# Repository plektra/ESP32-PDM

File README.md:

# ESP32-PDM

An open, low-cost power distribution module for boats: solid-state outputs controlled both by ordinary
panel switches and over NMEA 2000, with current and fault reporting. Built around an ESP32-S3 and
Infineon PROFET+24V high-side switches, for 12 V and 24 V systems, assembled by JLCPCB.

**Status:** Both boards (`hardware/pdm-4ch`, `hardware/pdm-hc2`) are complete at schematic level and pass ERC
(apart from library-version notices). The `pdm-4ch` PCB is fully routed (0 DRC errors, 0 unconnected); the image
above is rendered from it. Not tested in hardware. A first firmware for `pdm-4ch` (`firmware/`) builds and passes its host tests; it has not run on a board. `pdm-4ch` goes first as a prototype, with `pdm-hc2` layout
after its bring-up.

## Boards

| Board | Channels | Output stage | Continuous current per channel (estimate, 40 °C, vented) |
|---|---|---|---|
| `pdm-4ch` | 4 | Infineon PROFET+24V BTT6050-1ERA (first version, 16 A in total) | ≈ 4 A |
| `pdm-hc2` | 2 | TI TPS48110A-Q1 + back-to-back MOSFETs, built-in breaker ≈ 17.5 A / 146 ms (≈ 15–20 A over tolerances) | ≈ 15 A |

Both boards share the controller, power, NMEA 2000 and switch-input design.

## Population and ordering rule (`pdm-4ch`)

The first version of `pdm-4ch` is built with four BTT6050-1ERA (≈ 4 A per channel, 16 A in total). Heavy loads go on
`pdm-hc2`. A BTT6010-1ERA (≈ 8 A) option may return in a later revision; it is not supported on this version.

## Features

- Physical switch inputs drive the outputs directly in hardware: they keep working if the ESP32 or
  its 3.3 V supply fails. Surge-protected, 12 V and 24 V, suitable for long switch cables.
- NMEA 2000 (isolated CAN), USB-C for programming, Wi-Fi for Signal K / configuration / OTA.
- Per-channel current measurement and fault reporting.
- Low-power modes controlled over the bus.

## Important limitations

- **Not protected against load dump.** Onboard TVS diodes clamp short transients only. A load dump
  (battery disconnected while an alternator is charging, or a BMS disconnect) must be handled at system
  level: alternator protection device, field-disconnect battery switch, or a BMS that signals the
  charge source before disconnecting. Like most marine electronics, this device relies on that.
- **Not a circuit breaker.** Every output wire must be protected by a fuse or breaker sized to the
  wire. The switches protect themselves, not your wiring.
- Install in an enclosed, ventilated location; observe the continuous current ratings.
- **Panel switches: dry contacts only.** Use plain (unlit) switch contacts. A lamp or LED across the contacts leaks
  current that can switch the output on in hardware. Use the J5 LED lines for panel indication instead.
- **12 V systems, engine cranking:** the panel-switch path switches an output off when the switch voltage drops below
  about 8 V (about 8.5 V at the battery). While the engine cranks, panel-switched outputs such as navigation lights can
  therefore go off for a moment. 24 V systems are not affected.
- **Reverse battery (`pdm-4ch`):** a reverse-blocking MOSFET in the supply input (Q30 with controller U30) keeps
  a reversed battery of up to 30 V away from the rest of the board, with no time limit: the bulk capacitor, the
  output switches, the panel switches and the loads see no reverse voltage. Above about 33 V the input surge diode
  conducts and the battery fuse must clear. If that MOSFET has failed short, the old limits apply: only the output
  switches survive (at most 28 V, under 2 minutes, each load at least 12 Ω), and the bulk capacitor C31 is not rated
  for reverse voltage and can overheat and vent. So check the polarity before connecting.
- **`pdm-hc2` external breaker (required):** each HC2 output must have its own external breaker or fuse that trips at
  **at most 15–18 A** (within minutes), in addition to the wire protection above. The built-in breaker trips at about
  17.5 A (≈ 15–20 A over part tolerances) only after 146 ms; between the 15 A rating and that level the board relies on
  the external breaker and the firmware soft fuse. The board label states the same. A bilge-pump output's breaker sits
  between J11 and the junction with the float-switch circuit, so the float circuit never depends on the PDM. That
  breaker must open before the float-circuit fuse: make it clearly smaller, or use a slower float fuse. Otherwise a
  short on the PDM side can also take out the float circuit.
- **`pdm-hc2` reverse battery destroys the board:** a reversed battery connection destroys both HC2 output controllers
  (TPS48110A-Q1, rated −1 V). There is no reverse-polarity protection on this revision. Use the keyed/polarised
  battery connector J10 only as marked, check polarity before connecting; the board label carries this warning.
- **Mounting:** two ways, on the same four M3 holes. On a DIN rail the bare board goes on a plastic carrier, edge-on, about 36 mm
  of rail per unit, inside an enclosure you provide; it must keep out drips and loose metal, and carrier and screws must never
  touch board copper. All connectors are keyed plugs that pull out from the board edge: wire them on the bench and leave room for the plug and cable bend. Exception: on the `pdm-4ch` prototype the battery connector J10 is a fixed screw terminal. Switch off the battery feed before unscrewing it, and on a DIN rail wire it before the neighbouring unit is fitted. Connect it only as marked: a reversed battery up to 30 V is blocked on the board, but check polarity before connecting.
  Alternatively use a vented 3D-printed enclosure, also for flat mounting. Each board gives off about 9 W at full load: in a
  shared enclosure keep the air inside at or below 50 °C for the full rating (estimate until measured), or derate.
- **Cable entry and strain relief:** no connector plug may carry a cable's weight or pull. Support every cable near the
  unit (a cable tie on the DIN mount's anchors, or the enclosure's glands and clamp), with a drip loop below the entry.
  The printed enclosure takes power and output cables through nylon glands and the thin panel wires through a clamp
  comb, all from the bottom face; the NMEA 2000 drop cable plugs into an M12 5-pin panel connector, whose shield pin is
  not connected: do not tie the drop's shield to anything at the PDM.
- **Board input limits:** at most **16 A** continuous through J10 on `pdm-4ch` and **36 A** on `pdm-hc2`, whatever the
  outputs could draw together. Size the battery feed, and its fuse, so that these limits are not exceeded.
- **`pdm-hc2` timing:** after power is connected, the first switch-on of each output (also from a panel switch)
  takes about 0.1 s. After an overcurrent or short-circuit trip the output stays off for about 4 minutes and then
  tries again. HC2 outputs are on/off only (no dimming/PWM).
- **`pdm-hc2` loads:** HC2 is for motor loads (bilge pumps, wipers) and LED work lights, one light per output. Each HC2 output is
  rated for at most **about 50 µF of load input capacitance** (to be confirmed on the prototype). A larger capacitive
  load can trip the short-circuit protection at switch-on, and the output then stays off for about 4 minutes. Put
  DC-DC converters (e.g. 24→12 V for a car radio), radios and other electronics on `pdm-4ch`. Put several lights on one
  output only if they have little capacitance (plain LED strips without their own driver) or a test shows the group
  switches on cleanly from warm; if a group trips at switch-on, split it over several outputs.
- **USB-C is a service port only.** Connect only a battery-powered laptop, or use a USB isolator. The
  board's GND is the boat's battery negative. A laptop on a shore-powered charger can tie its protective
  earth to battery negative through the USB cable, which can cause ground-loop currents, galvanic
  corrosion and damage. Unplug the USB cable after service.

## Installation

The interference immunity of the boards assumes the cable practice below. It adds to the points in
[Important limitations](#important-limitations) (load dump, wire fuses, dry contacts, reverse battery, the `pdm-hc2`
external breaker, USB service only), which are not repeated here.

- **Battery feed.** Fuse at the battery, sized to the wire. Run + and − as a twisted or tightly bundled pair, as short
  as possible, at least 0.5 m from the VHF antenna feed and the transmitter; where they must cross, cross at 90°.
  Check polarity before connecting (see the reverse-battery points above).
- **Loads.** Run each load's return with its feed (same cable, twisted) back to the battery negative bus. Never return
  load current through the PDM ground. Fuse each output wire (see "Not a circuit breaker" above).
- **Inductive loads** (solenoids, relays, horns, motors): fit a diode or TVS at the load.
- **PWM.** No PWM above 200 Hz on `pdm-4ch`. No PWM at all on `pdm-hc2` until it has been measured on the bench
  (its outputs are on/off only, see above).
- **Panel cable.** One screened multicore, at most 10 m, with the switch, LED and supply wires inside the same cable.
  Connect the drain only at the PDM end (J5.10). Dry contacts only (see above). Do not share the cable with other
  loads.
- **NMEA 2000.** Drop cable at most 6 m; ground the backbone shield once, at the power tap. The node has no shield pin,
  so do not connect the drain at the node. Keep the drop away from the VHF coax.
- **Position.** An enclosed, vented box (see above), as far from the VHF antenna and its coax as practical. The plastic
  box gives no shielding: the cables act as the antenna, so cable practice matters more than box position.

## Repository layout

```
hardware/pdm-4ch/   KiCad project, 4-channel board (PROFET)
hardware/pdm-hc2/   KiCad project, 2-channel high-current board
lib/                shared KiCad symbols and footprints
docs/               CONTINUE-FROM-HERE (next steps), decisions, ARCHITECTURE, design notes, reviews
tools/              heat budget model, schematic editing helpers, netlist checker
.claude/            Claude Code roles: commands and review agents (see docs/WORKING-WITH-CLAUDE.md)
```

See [docs/design-notes.md](docs/design-notes.md) for the design rationale, heat budget and open items.

## History

This repository supersedes the earlier two-board design (base board + output module):
[ESP32-PDM-base](https://github.com/plektra/ESP32-PDM-base) and
[ESP32-PDM-4x4](https://github.com/plektra/ESP32-PDM-4x4).

## License

Hardware (schematics, PCB, fabrication files, documentation, library parts): [CERN-OHL-S v2](LICENSE).
Software (`tools/`, board scripts, firmware): [MIT](LICENSE-MIT). Third-party 3D models and KiCad stock-library
parts keep their own terms. Versions up to commit `1799052` (2026-11-17) were released under MIT. Details, and the
source-location notice for anyone who makes boards from these files: [NOTICE.md](NOTICE.md).

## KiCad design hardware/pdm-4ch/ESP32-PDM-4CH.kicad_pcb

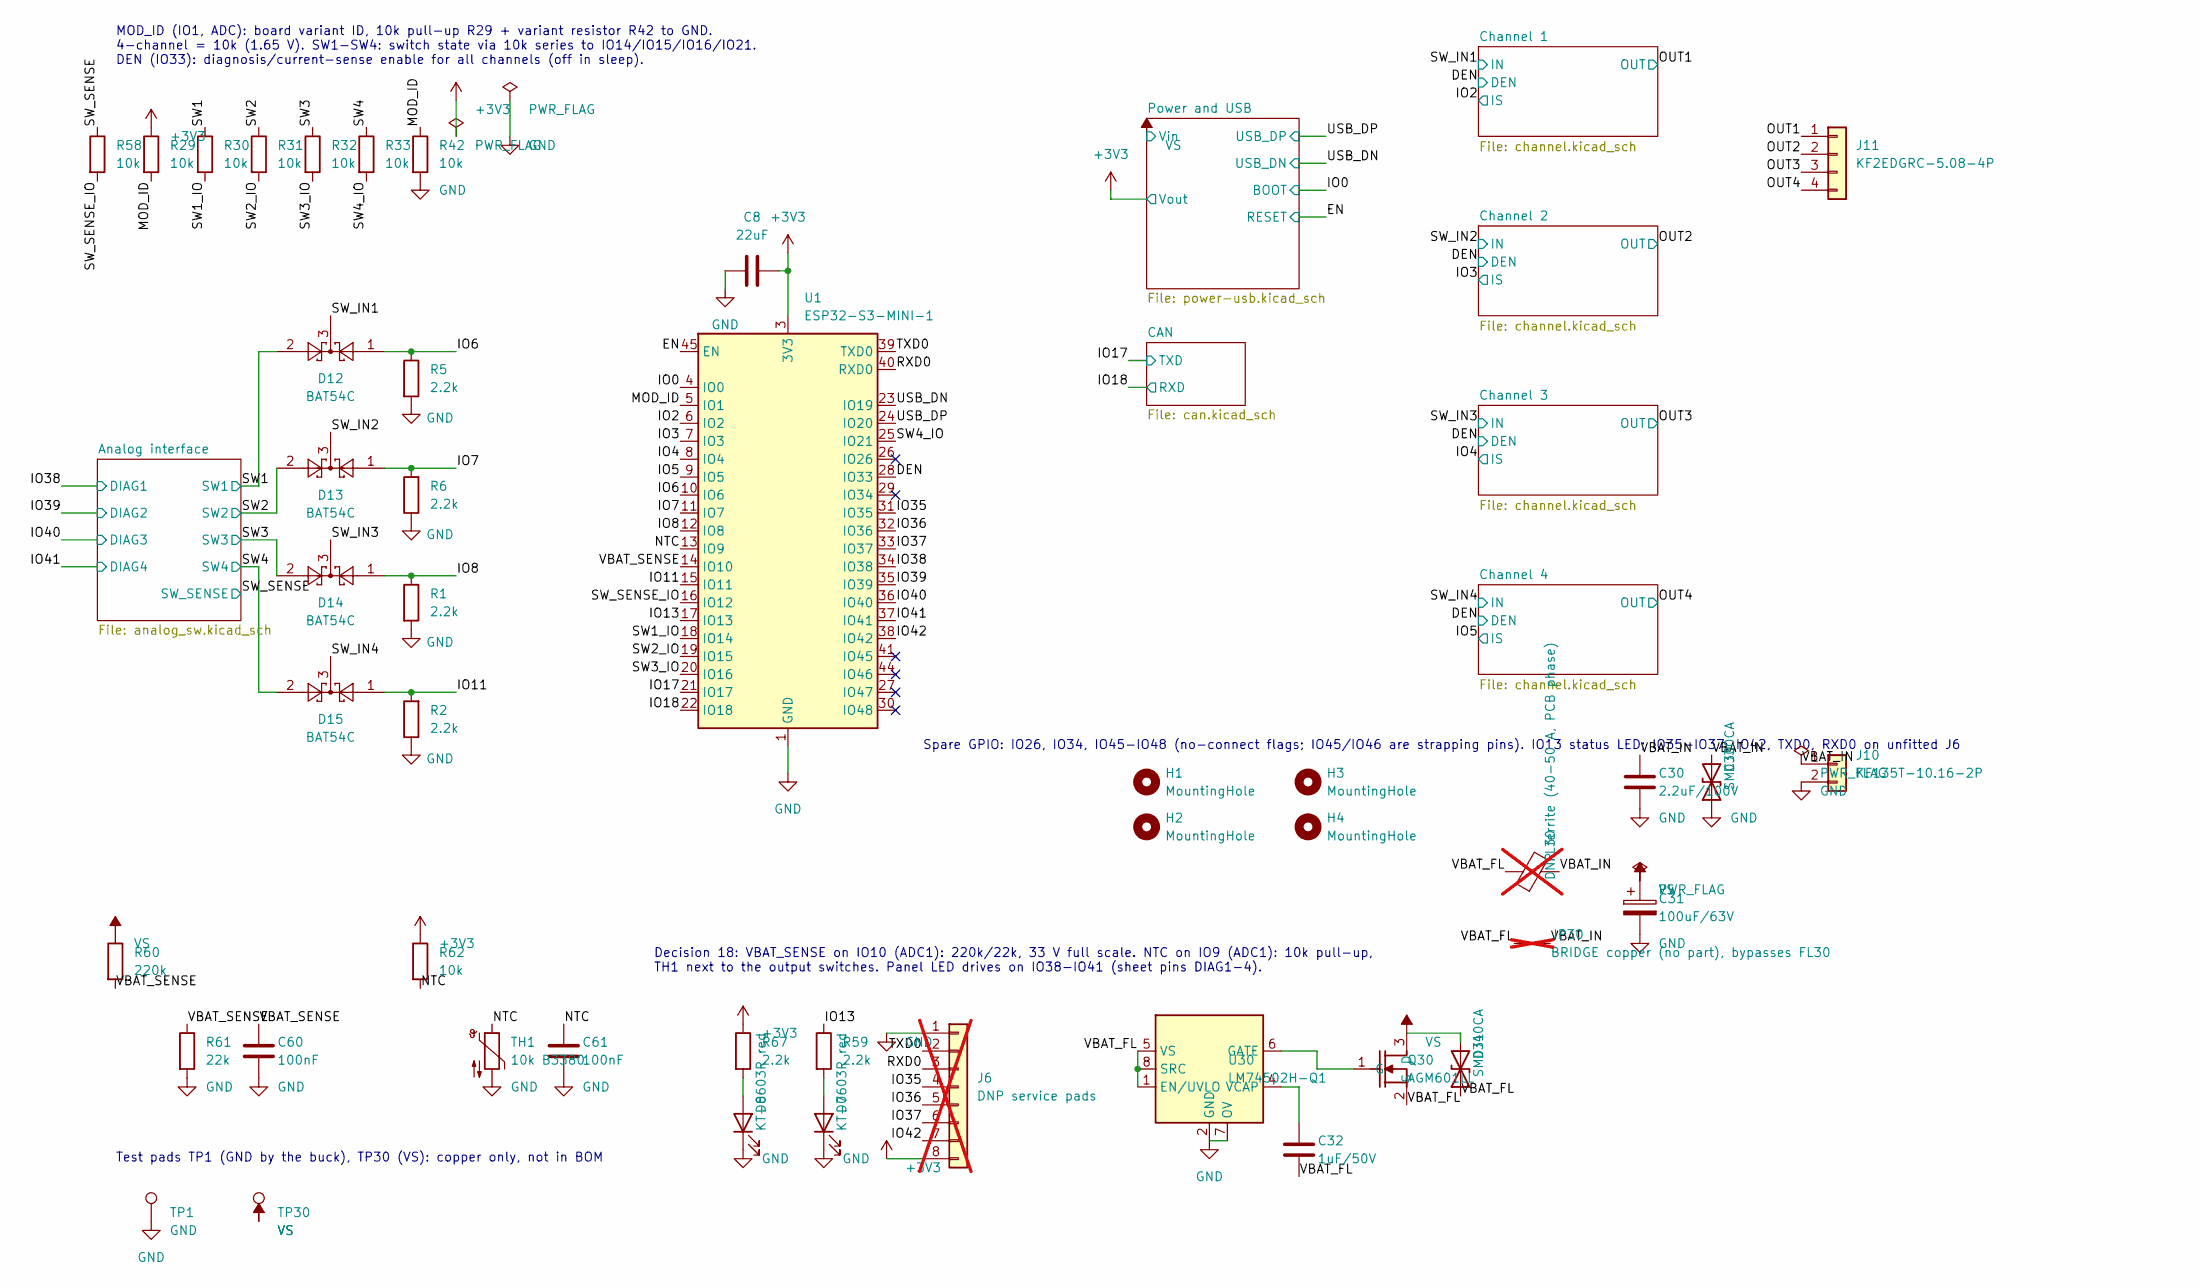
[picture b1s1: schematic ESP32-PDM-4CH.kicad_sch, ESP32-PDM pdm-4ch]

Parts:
C8: 22uF; C_0805_2012Metric; LCSC C45783
C30: 2.2uF/100V; C_1206_3216Metric; MPN Samsung CL31B225KCHSNNE; LCSC C170101
C31: 100uF/63V; CP_Elec_8x10; MPN Ymin VKMD1001J101MV; LCSC C487384
C32: 1uF/50V; C_0603_1608Metric; LCSC C15849
C60, C61: 100nF; C_0402_1005Metric; LCSC C307331
D7, D8: KT-0603R red; LED_0603_1608Metric; LCSC C2286
D12, D13, D14, D15: BAT54C; SOT-23; LCSC C22466350
D30: SMCJ30CA; D_SMC; LCSC C19077607
D31: SMDJ40CA; D_SMC; LCSC C42371557
FL30: DNP ferrite (40-50 A, PCB phase); not fitted
H1, H2, H3, H4: MountingHole; MountingHole_3.2mm_M3
J6: DNP service pads; PinHeader_1x08_P2.54mm_Vertical; not fitted
J10: KF135T-10.16-2P; Kefa_KF135T-10.16-2P; LCSC C475108
J11: KF2EDGRC-5.08-4P; Kefa_KF2EDGRC-5.08-4P; LCSC C441238
JP30: BRIDGE copper (no part), bypasses FL30; NetTie-2_SMD_Pad2.0mm; not fitted
Q30: AGM601LL; Infineon_PG-HSOF-8-1; LCSC C5464765
R1, R2, R5, R6, R59, R67: 2.2k; R_0402_1005Metric; LCSC C25879
R29, R30, R31, R32, R33, R42, R58, R62: 10k; R_0402_1005Metric; LCSC C25744
R60: 220k; R_0402_1005Metric; LCSC C25767
R61: 22k; R_0402_1005Metric; LCSC C25768
TH1: 10k B3380; R_0603_1608Metric; LCSC C52155402
TP1: GND; TestPoint_Pad_D1.0mm
TP30: VS; TestPoint_Pad_D1.0mm
U1: ESP32-S3-MINI-1; ESP32-S2-MINI-1; LCSC C2913206
U30: LM74502H-Q1; TI_DDF0008A; MPN LM74502HQDDFRQ1; LCSC C5219203

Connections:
+3V3: C8.2, J6.8, R29.1, R62.1, R67.1, U1.3 (3V3); also elsewhere on the board
/DEN: U1.28 (IO33); also elsewhere on the board
/EN: U1.45 (EN); also elsewhere on the board
/IO0: U1.4 (IO0); also elsewhere on the board
/IO2: U1.6 (IO2); also elsewhere on the board
/IO3: U1.7 (IO3); also elsewhere on the board
/IO4: U1.8 (IO4); also elsewhere on the board
/IO5: U1.9 (IO5); also elsewhere on the board
/IO6: D12.1, R5.1, U1.10 (IO6)
/IO7: D13.1, R6.2, U1.11 (IO7)
/IO8: D14.1, R1.1, U1.12 (IO8)
/IO11: D15.1, R2.2, U1.15 (IO11)
/IO13: R59.1, U1.17 (IO13)
/IO17: U1.21 (IO17); also elsewhere on the board
/IO18: U1.22 (IO18); also elsewhere on the board
/IO35: J6.4, U1.31 (IO35)
/IO36: J6.5, U1.32 (IO36)
/IO37: J6.6, U1.33 (IO37)
/IO38: U1.34 (IO38); also elsewhere on the board
/IO39: U1.35 (IO39); also elsewhere on the board
/IO40: U1.36 (IO40); also elsewhere on the board
/IO41: U1.37 (IO41); also elsewhere on the board
/IO42: J6.7, U1.38 (IO42)
/MOD_ID: R29.2, R42.1, U1.5 (IO1)
/NTC: C61.1, R62.2, TH1.1, U1.13 (IO9)
/OUT1: J11.1; also elsewhere on the board
/OUT2: J11.2; also elsewhere on the board
/OUT3: J11.3; also elsewhere on the board
/OUT4: J11.4; also elsewhere on the board
/RXD0: J6.3, U1.40 (RXD0)
/SW1: D12.2, R30.1; also elsewhere on the board
/SW1_IO: R30.2, U1.18 (IO14)
/SW2: D13.2, R31.1; also elsewhere on the board
/SW2_IO: R31.2, U1.19 (IO15)
/SW3: D14.2, R32.1; also elsewhere on the board
/SW3_IO: R32.2, U1.20 (IO16)
/SW4: D15.2, R33.1; also elsewhere on the board
/SW4_IO: R33.2, U1.25 (IO21)
/SW_IN1: D12.3; also elsewhere on the board
/SW_IN2: D13.3; also elsewhere on the board
/SW_IN3: D14.3; also elsewhere on the board
/SW_IN4: D15.3; also elsewhere on the board
/SW_SENSE: R58.1; also elsewhere on the board
/SW_SENSE_IO: R58.2, U1.16 (IO12)
/TXD0: J6.2, U1.39 (TXD0)
/USB_DN: U1.23 (IO19); also elsewhere on the board
/USB_DP: U1.24 (IO20); also elsewhere on the board
/VBAT_FL: C32.2, D31.1 (A1), FL30.1, JP30.1, Q30.2 (S), U30.1 (EN/UVLO), U30.5 (VS), U30.8 (SRC)
/VBAT_IN: C30.1, D30.2 (A2), FL30.2, J10.1, JP30.2
/VBAT_SENSE: C60.1, R60.2, R61.1, U1.14 (IO10)
GND: C8.1, C30.2, C31.2, C60.2, C61.2, D7.1 (K), D8.1 (K), D30.1 (A1), J6.1, J10.2, R1.2, R2.1, R5.2, R6.1, R42.2, R61.2, TH1.2, TP1.1, U1.1 (GND), U1.2 (GND), U1.42 (GND), U1.43 (GND), U1.46 (GND), U1.47 (GND), U1.48 (GND), U1.49 (GND), U1.50 (GND), U1.51 (GND), U1.52 (GND), U1.53 (GND), U1.54 (GND), U1.55 (GND), U1.56 (GND), U1.57 (GND), U1.58 (GND), U1.59 (GND), U1.60 (GND), U1.61 (GND), U1.62 (GND), U1.63 (GND), U1.64 (GND), U1.65 (GND), U30.2 (GND), U30.7 (OV); also elsewhere on the board
unnamed: D7.2 (A), R59.2
unnamed: D8.2 (A), R67.2
unnamed: Q30.1 (G), U30.6 (GATE)
unnamed: C32.1, U30.4 (VCAP)
VS: C31.1, D31.2 (A2), Q30.3 (D), R60.1, TP30.1; also elsewhere on the board

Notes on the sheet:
MOD_ID (IO1, ADC): board variant ID, 10k pull-up R29 + variant resistor R42 to GND. 4-channel = 10k (1.65 V). SW1-SW4: switch state via 10k series to IO14/IO15/IO16/IO21. DEN (IO33): diagnosis/current-sense enable for all channels (off in sleep).
Spare GPIO: IO26, IO34, IO45-IO48 (no-connect flags; IO45/IO46 are strapping pins). IO13 status LED; IO35-IO37, IO42, TXD0, RXD0 on unfitted J6
Decision 18: VBAT_SENSE on IO10 (ADC1): 220k/22k, 33 V full scale. NTC on IO9 (ADC1): 10k pull-up, TH1 next to the output switches. Panel LED drives on IO38-IO41 (sheet pins DIAG1-4).
Test pads TP1 (GND by the buck), TP30 (VS): copper only, not in BOM

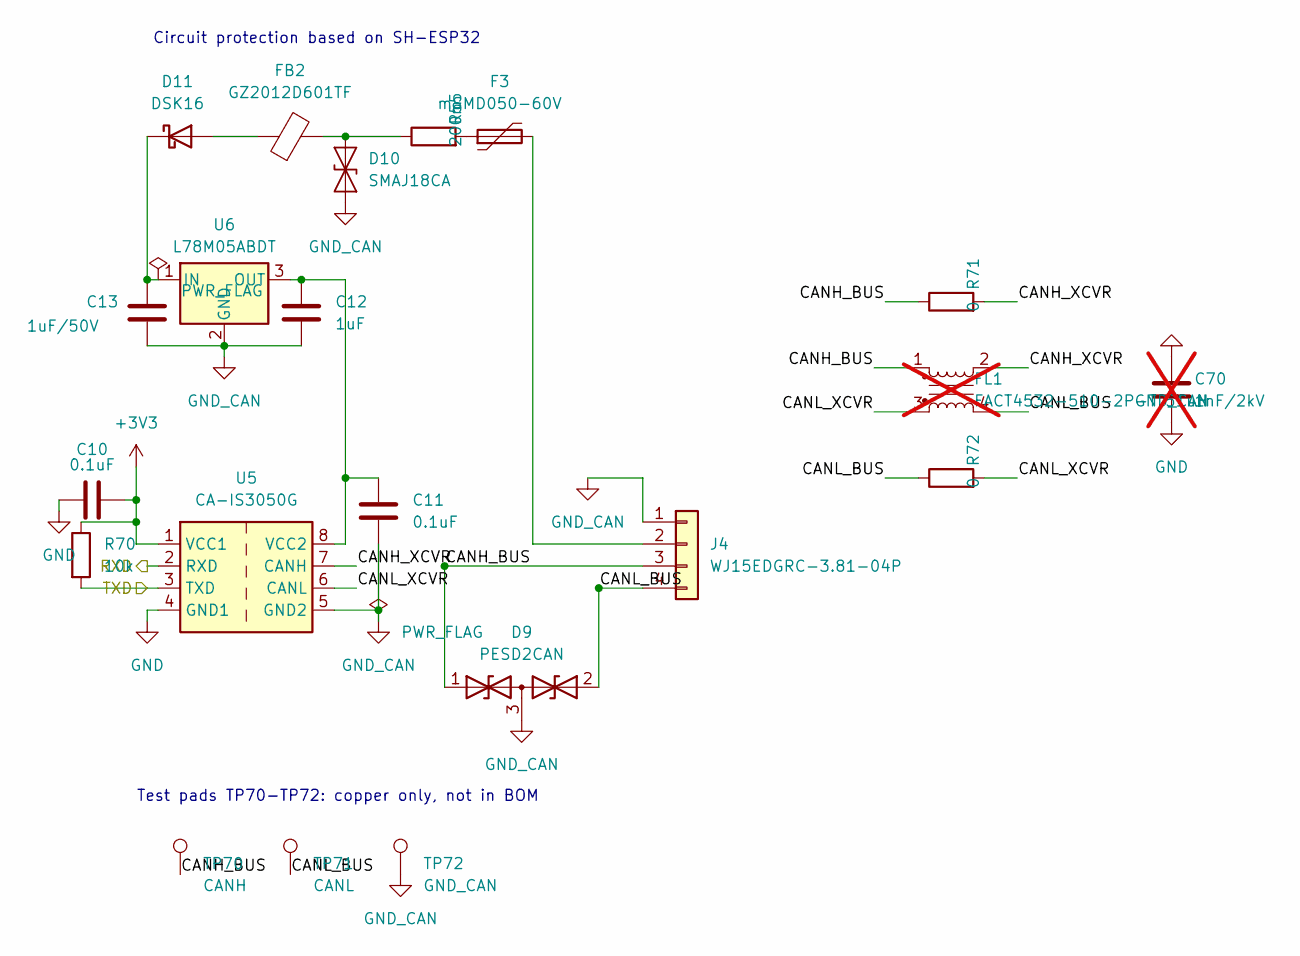
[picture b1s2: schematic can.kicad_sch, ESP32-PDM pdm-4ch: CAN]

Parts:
C10, C11: 0.1uF; C_0402_1005Metric; LCSC C307331
C12: 1uF; C_0603_1608Metric; LCSC C15849
C13: 1uF/50V; C_0805_2012Metric; LCSC C28323
C70: 1nF/2kV; C_1206_3216Metric; LCSC C9196; not fitted
D9: PESD2CAN; SOT-23; LCSC C2687131
D10: SMAJ18CA; D_SMA; LCSC C19077539
D11: DSK16; D_SOD-123F; LCSC C22466351
F3: mSMD050-60V; Fuse_1812_4532Metric; LCSC C70113
FB2: GZ2012D601TF; L_0805_2012Metric; LCSC C1017
FL1: FACT4532-510-2P-T 51uH; L_CommonModeChoke_Coilank_ACM4532; LCSC C20624726; not fitted
J4: WJ15EDGRC-3.81-04P; Kangnex_WJ15EDGRC-3.81-04P; LCSC C7245
R55: 200m; R_2512_6332Metric; LCSC C7420022
R70: 10k; R_0402_1005Metric; LCSC C25744
R71, R72: 0; R_0402_1005Metric; LCSC C17168
TP70: CANH; TestPoint_Pad_D1.0mm
TP71: CANL; TestPoint_Pad_D1.0mm
TP72: GND_CAN; TestPoint_Pad_D1.0mm
U5: CA-IS3050G; SOIC-8_7.5x5.85mm_P1.27mm; LCSC C528763
U6: L78M05ABDT; TO-252-2; LCSC C58069

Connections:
+3V3: C10.2, R70.1, U5.1 (VCC1); also elsewhere on the board
/CAN/CANH_BUS: D9.1 (A1), FL1.1, J4.3, R71.1, TP70.1
/CAN/CANH_XCVR: FL1.2, R71.2, U5.7 (CANH)
/CAN/CANL_BUS: D9.2 (A2), FL1.4, J4.4, R72.1, TP71.1
/CAN/CANL_XCVR: FL1.3, R72.2, U5.6 (CANL)
/IO17: R70.2, U5.3 (TXD); also elsewhere on the board
/IO18: U5.2 (RXD); also elsewhere on the board
GND: C10.1, C70.2, U5.4 (GND1); also elsewhere on the board
GND_CAN: C11.2, C12.2, C13.2, C70.1, D9.3 (common), D10.1 (A1), J4.1, TP72.1, U5.5 (GND2), U6.2 (GND)
unnamed: D10.2 (A2), FB2.2, R55.1
unnamed: D11.2 (A), FB2.1
unnamed: C13.1, D11.1 (K), U6.1 (IN)
unnamed: F3.1, R55.2
unnamed: F3.2, J4.2
unnamed: C11.1, C12.1, U5.8 (VCC2), U6.3 (OUT)

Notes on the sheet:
Circuit protection based on SH-ESP32
Test pads TP70-TP72: copper only, not in BOM

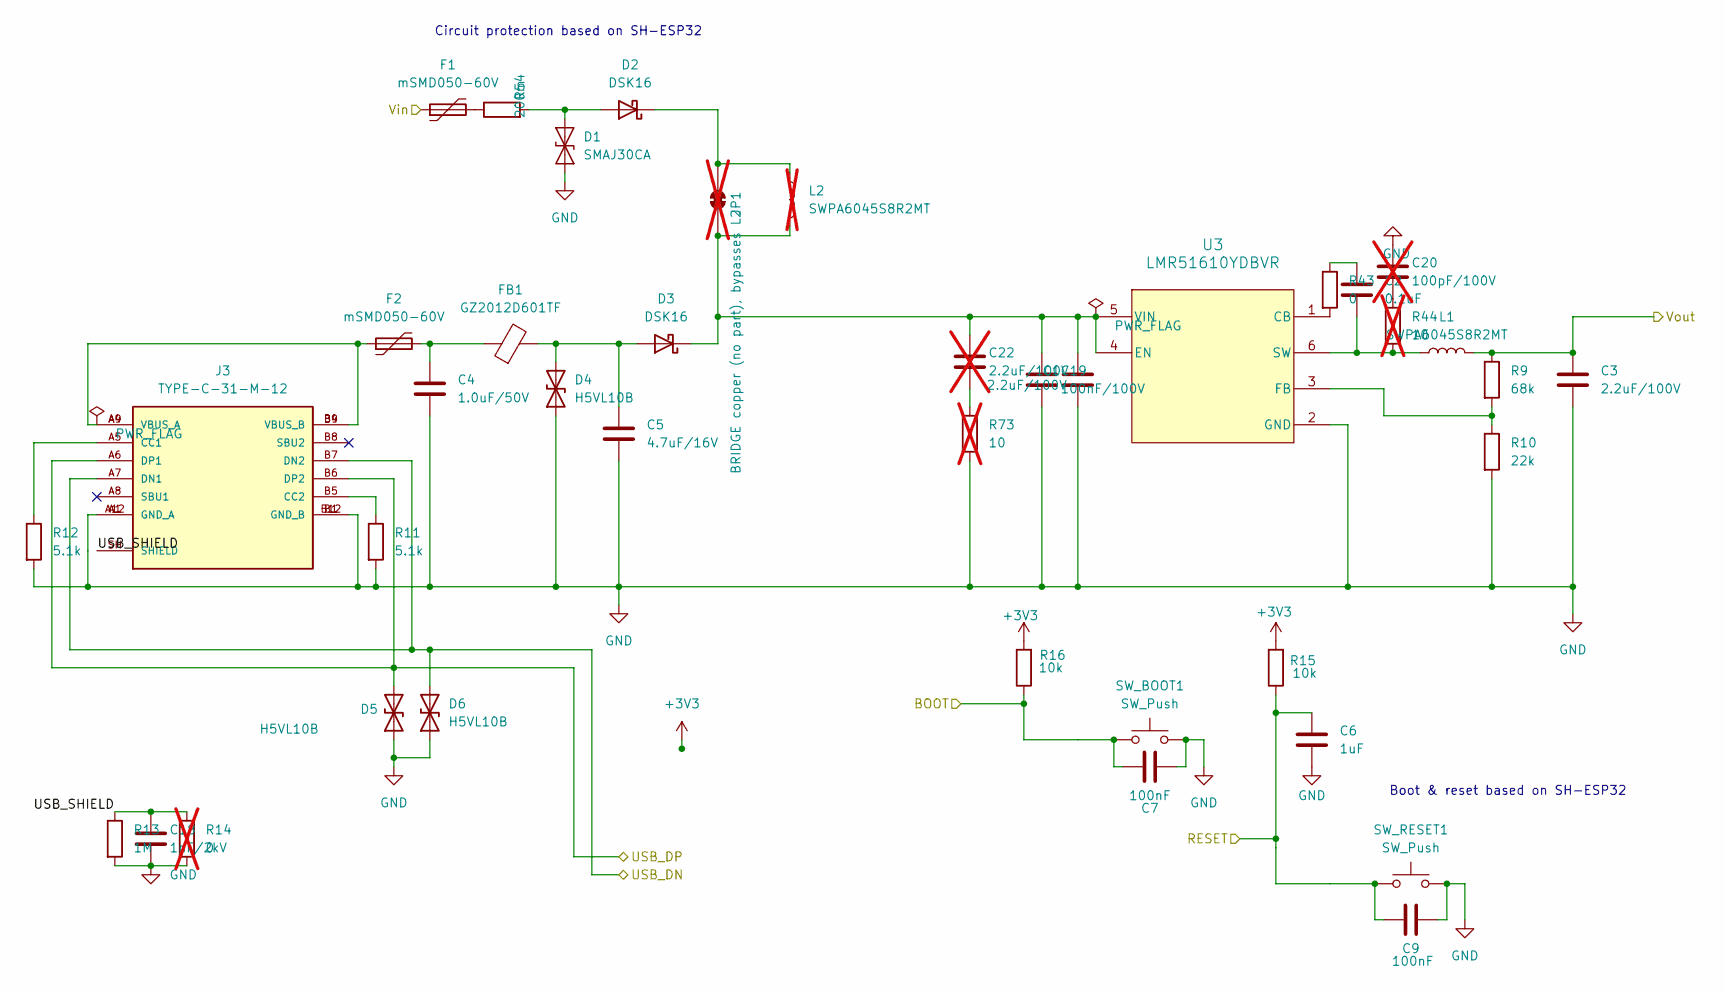
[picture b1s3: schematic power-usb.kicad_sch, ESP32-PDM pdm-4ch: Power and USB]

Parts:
C1, C3: 2.2uF/100V; C_1206_3216Metric; LCSC C170101
C2: 0.1uF; C_0402_1005Metric; LCSC C307331
C4: 1.0uF/50V; C_0603_1608Metric; LCSC C15849
C5: 4.7uF/16V; C_0603_1608Metric; LCSC C19666
C6: 1uF; C_0603_1608Metric; LCSC C15849
C7, C9: 100nF; C_0805_2012Metric; LCSC C28233
C18: 1nF/2kV; C_1206_3216Metric; LCSC C9196
C19: 100nF/100V; C_0805_2012Metric; LCSC C28233
C20: 100pF/100V; C_0603_1608Metric; LCSC C296717; not fitted
C22: 2.2uF/100V; C_1206_3216Metric; LCSC C170101; not fitted
D1: SMAJ30CA; D_SMA; LCSC C19077548
D2, D3: DSK16; D_SOD-123F; LCSC C22466351
D4, D5, D6: H5VL10B; D_SOD-882; LCSC C7420372
F1, F2: mSMD050-60V; Fuse_1812_4532Metric; LCSC C70113
FB1: GZ2012D601TF; L_0805_2012Metric; LCSC C1017
J3: TYPE-C-31-M-12; USB_C_Receptacle_HRO_TYPE-C-31-M-12; PARTREV A2; LCSC C165948
JP1: BRIDGE copper (no part), bypasses L2; SolderJumper-2_P1.3mm_Bridged_Pad1.0x1.5mm; not fitted
L1: SWPA6045S8R2MT; L_Sunlord_SWPA6045S; LCSC C96963
L2: SWPA6045S8R2MT; L_Sunlord_SWPA6045S; LCSC C96963; not fitted
R9: 68k; R_0402_1005Metric; LCSC C36871
R10: 22k; R_0402_1005Metric; LCSC C25768
R11, R12: 5.1k; R_0402_1005Metric; LCSC C25905
R13: 1M; R_1206_3216Metric; LCSC C17927
R14: 0; R_0603_1608Metric; LCSC C21189; not fitted
R15, R16: 10k; R_0402_1005Metric; LCSC C25744
R43: 0; R_0402_1005Metric; LCSC C17168
R44, R73: 10; R_1206_3216Metric; LCSC C17903; not fitted
R54: 200m; R_2512_6332Metric; LCSC C7420022
SW_BOOT1: SW_Push; SW_Push_1P1T_XKB_TS-1187A; LCSC C318884
SW_RESET1: SW_Push; SW_Push_1P1T_XKB_TS-1187A; LCSC C318884
U3: LMR51610YDBVR; SOT-23-6; LCSC C22427220

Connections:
+3V3: C3.1, L1.2, R9.1, R15.2, R16.2; also elsewhere on the board
/EN: C6.1, C9.1, R15.1, SW_RESET1.1; also elsewhere on the board
/IO0: C7.2, R16.1, SW_BOOT1.1; also elsewhere on the board
/Power and USB/USB_SHIELD: C18.1, J3.SH (SHIELD), R13.1, R14.1
/USB_DN: D6.2 (A2), J3.A7 (DN1), J3.B7 (DN2); also elsewhere on the board
/USB_DP: D5.2 (A2), J3.A6 (DP1), J3.B6 (DP2); also elsewhere on the board
GND: C1.1, C3.2, C4.2, C5.2, C6.2, C7.1, C9.2, C18.2, C19.2, C20.1, D1.1 (A1), D4.1 (A1), D5.1 (A1), D6.1 (A1), J3.A1 (GND_A), J3.A12 (GND_A), J3.B1 (GND_B), J3.B12 (GND_B), R10.2, R11.2, R12.2, R13.2, R14.2, R73.2, SW_BOOT1.2, SW_RESET1.2, U3.2 (GND); also elsewhere on the board
unnamed: C2.1, R43.1
unnamed: C4.1, F2.2, FB1.1
unnamed: C20.2, R44.1
unnamed: C22.2, R73.1
unnamed: D1.2 (A2), D2.2 (A), R54.2
unnamed: D2.1 (K), JP1.1 (A), L2.1
unnamed: C5.1, D3.2 (A), D4.2 (A2), FB1.2
unnamed: C1.2, C19.1, C22.1, D3.1 (K), JP1.2 (B), L2.2, U3.4 (EN), U3.5 (VIN)
unnamed: F1.2, R54.1
unnamed: F2.1, J3.A4 (VBUS_A), J3.A9 (VBUS_A), J3.B4 (VBUS_B), J3.B9 (VBUS_B)
unnamed: J3.A5 (CC1), R12.1
unnamed: J3.B5 (CC2), R11.1
unnamed: R43.2, U3.1 (CB)
unnamed: R9.2, R10.1, U3.3 (FB)
unnamed: C2.2, L1.1, R44.2, U3.6 (SW)
VS: F1.1; also elsewhere on the board

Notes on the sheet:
Circuit protection based on SH-ESP32
Boot & reset based on SH-ESP32

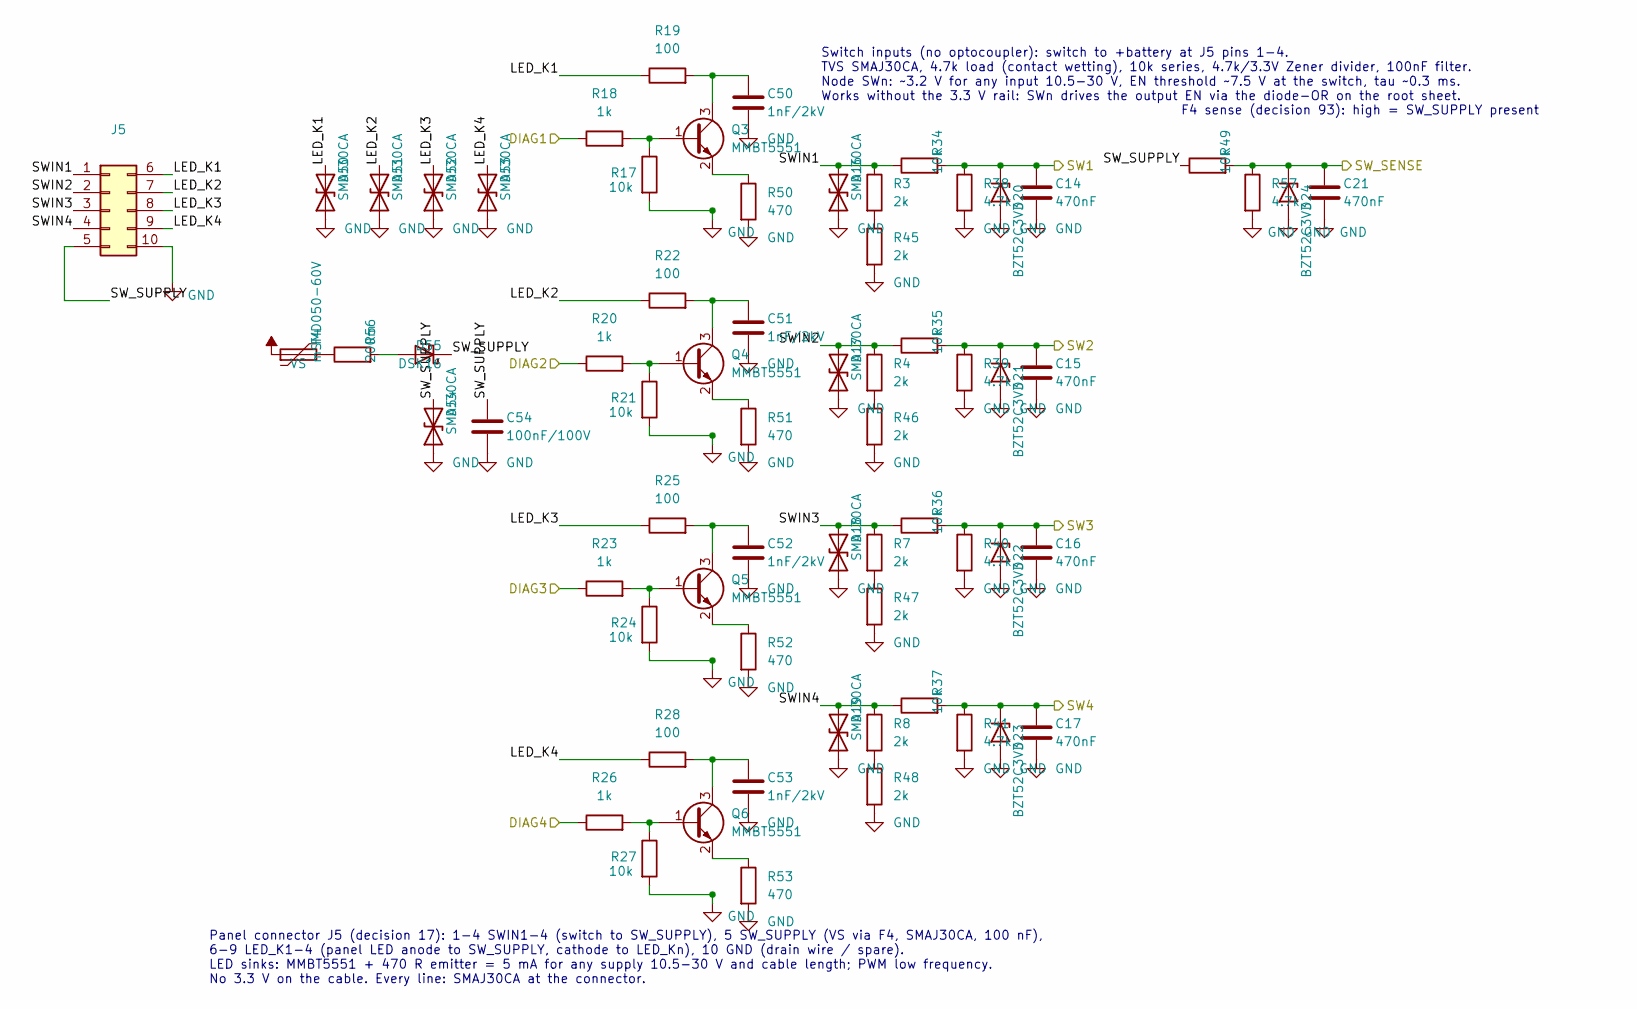
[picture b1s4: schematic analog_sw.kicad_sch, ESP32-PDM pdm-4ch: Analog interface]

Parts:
C14, C15, C16, C17, C21: 470nF; C_0402_1005Metric; LCSC C47339
C50, C51, C52, C53: 1nF/2kV; C_1206_3216Metric; LCSC C9196
C54: 100nF/100V; C_0805_2012Metric; LCSC C28233
D16, D17, D18, D19, D50, D51, D52, D53, D54: SMAJ30CA; D_SMA; LCSC C19077548
D20, D21, D22, D23, D24: BZT52C3V3; D_SOD-123; LCSC C19077396
D55: DSK16; D_SOD-123F; LCSC C22466351
F4: mSMD050-60V; Fuse_1812_4532Metric; LCSC C70113
J5: WJ15EDGRC-3.81-10P; Kangnex_WJ15EDGRC-3.81-10P; LCSC C26895
Q3, Q4, Q5, Q6: MMBT5551; SOT-23-3; LCSC C2145
R3, R4, R7, R8, R45, R46, R47, R48: 2k; R_1206_3216Metric; LCSC C17944
R17, R21, R24, R27: 10k; R_0402_1005Metric; LCSC C25744
R18, R20, R23, R26: 1k; R_0402_1005Metric; LCSC C11702
R19, R22, R25, R28: 100; R_0402_1005Metric; LCSC C25076
R34, R35, R36, R37, R49: 10k; R_1206_3216Metric; LCSC C17902
R38, R39, R40, R41, R57: 4.7k; R_0402_1005Metric; LCSC C25900
R50, R51, R52, R53: 470; R_0402_1005Metric; LCSC C25117
R56: 200m; R_2512_6332Metric; LCSC C7420022

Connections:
/Analog interface/LED_K1: D50.2 (A2), J5.6, R19.1
/Analog interface/LED_K2: D51.2 (A2), J5.7, R22.1
/Analog interface/LED_K3: D52.2 (A2), J5.8, R25.1
/Analog interface/LED_K4: D53.2 (A2), J5.9, R28.1
/Analog interface/SWIN1: D16.2 (A2), J5.1, R3.1, R34.1
/Analog interface/SWIN2: D17.2 (A2), J5.2, R4.1, R35.1
/Analog interface/SWIN3: D18.2 (A2), J5.3, R7.1, R36.1
/Analog interface/SWIN4: D19.2 (A2), J5.4, R8.1, R37.1
/Analog interface/SW_SUPPLY: C54.1, D54.2 (A2), D55.1 (K), J5.5, R49.1
/IO38: R18.1; also elsewhere on the board
/IO39: R20.1; also elsewhere on the board
/IO40: R23.1; also elsewhere on the board
/IO41: R26.1; also elsewhere on the board
/SW1: C14.1, D20.1 (K), R34.2, R38.1; also elsewhere on the board
/SW2: C15.1, D21.1 (K), R35.2, R39.1; also elsewhere on the board
/SW3: C16.1, D22.1 (K), R36.2, R40.1; also elsewhere on the board
/SW4: C17.1, D23.1 (K), R37.2, R41.1; also elsewhere on the board
/SW_SENSE: C21.1, D24.1 (K), R49.2, R57.1; also elsewhere on the board
GND: C14.2, C15.2, C16.2, C17.2, C21.2, C50.2, C51.2, C52.2, C53.2, C54.2, D16.1 (A1), D17.1 (A1), D18.1 (A1), D19.1 (A1), D20.2 (A), D21.2 (A), D22.2 (A), D23.2 (A), D24.2 (A), D50.1 (A1), D51.1 (A1), D52.1 (A1), D53.1 (A1), D54.1 (A1), J5.10, R17.2, R21.2, R24.2, R27.2, R38.2, R39.2, R40.2, R41.2, R45.2, R46.2, R47.2, R48.2, R50.2, R51.2, R52.2, R53.2, R57.2; also elsewhere on the board
unnamed: D55.2 (A), R56.2
unnamed: F4.2, R56.1
unnamed: Q3.1 (B), R17.1, R18.2
unnamed: C50.1, Q3.3 (C), R19.2
unnamed: Q3.2 (E), R50.1
unnamed: Q4.1 (B), R20.2, R21.1
unnamed: C51.1, Q4.3 (C), R22.2
unnamed: Q4.2 (E), R51.1
unnamed: Q5.1 (B), R23.2, R24.1
unnamed: C52.1, Q5.3 (C), R25.2
unnamed: Q5.2 (E), R52.1
unnamed: Q6.1 (B), R26.2, R27.1
unnamed: C53.1, Q6.3 (C), R28.2
unnamed: Q6.2 (E), R53.1
unnamed: R3.2, R45.1
unnamed: R4.2, R46.1
unnamed: R7.2, R47.1
unnamed: R8.2, R48.1
VS: F4.1; also elsewhere on the board

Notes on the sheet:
Switch inputs (no optocoupler): switch to +battery at J5 pins 1-4. TVS SMAJ30CA, 4.7k load (contact wetting), 10k series, 4.7k/3.3V Zener divider, 100nF filter. Node SWn: ~3.2 V for any input 10.5-30 V, EN threshold ~7.5 V at the switch, tau ~0.3 ms. Works without the 3.3 V rail: SWn drives the out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
Panel connector J5 (decision 17): 1-4 SWIN1-4 (switch to SW_SUPPLY), 5 SW_SUPPLY (VS via F4, SMAJ30CA, 100 nF), 6-9 LED_K1-4 (panel LED anode to SW_SUPPLY, cathode to LED_Kn), 10 GND (drain wire / spare). LED sinks: MMBT5551 + 470 R emitter = 5 mA for any supply 10.5-30 V and cable length; PWM low 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
F4 sense (decision 93): high = SW_SUPPLY present

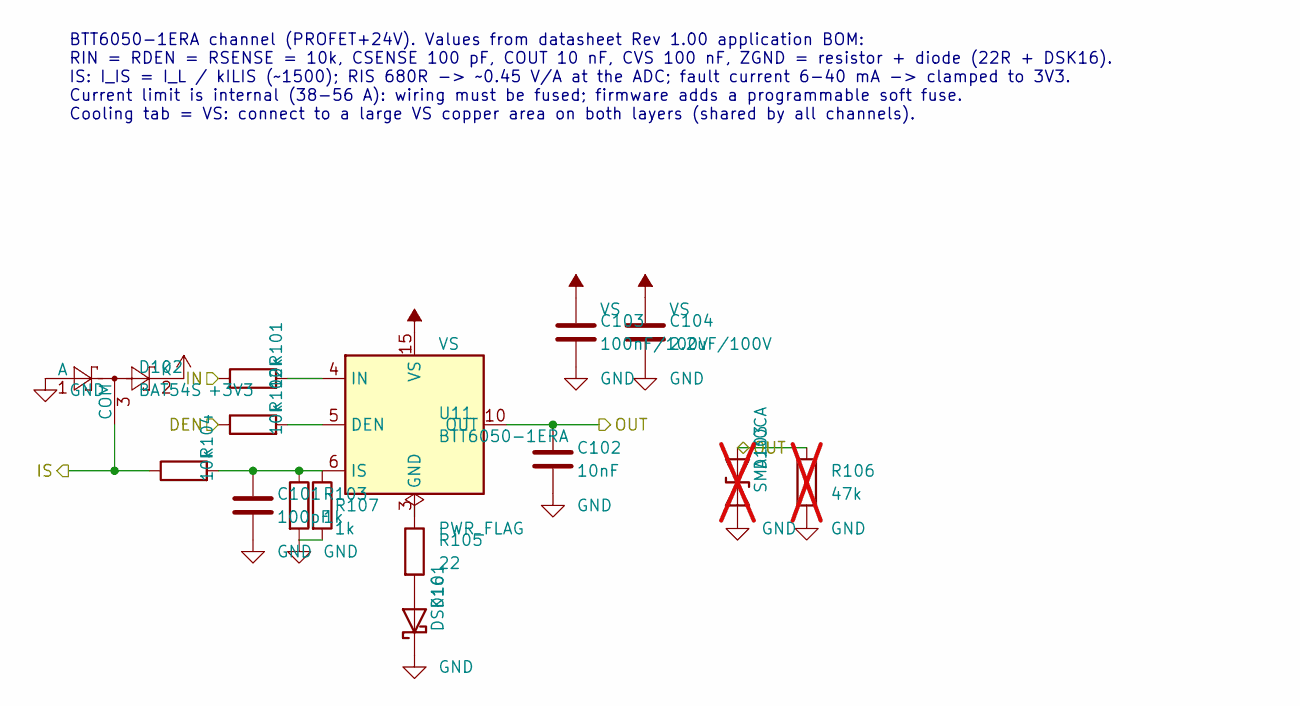
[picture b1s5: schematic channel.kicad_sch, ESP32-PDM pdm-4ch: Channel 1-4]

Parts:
C101: 100pF; C_0402_1005Metric; LCSC C1546
C102: 10nF; C_0402_1005Metric; LCSC C15195
C103: 100nF/100V; C_0805_2012Metric; LCSC C28233
C104: 2.2uF/100V; C_1206_3216Metric; MPN Samsung CL31B225KCHSNNE; LCSC C170101
D101: DSK16; D_SOD-123F; LCSC C22466351
D102: BAT54S; SOT-23; LCSC C7420333
D103: SMAJ30CA; D_SMA; LCSC C19077548; not fitted
R101, R102, R104: 10k; R_0402_1005Metric; LCSC C25744
R103, R107: 1k; R_1206_3216Metric; MPN CRCW12061K00FKEAHP; LCSC C844867
R105: 22; R_0402_1005Metric; LCSC C25092
R106: 47k; R_0603_1608Metric; LCSC C25819; not fitted
U11: BTT6050-1ERA; Infineon_PG-TDSO-14_ThermalVias; LCSC C534868

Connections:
+3V3: D102.2 (K); also elsewhere on the board
/DEN: R102.1; also elsewhere on the board
/IO2: D102.3 (COM), R104.1; also elsewhere on the board
/OUT1: C102.1, D103.2 (A2), R106.1, U11.10 (OUT), U11.11 (OUT), U11.12 (OUT); also elsewhere on the board
/SW_IN1: R101.1; also elsewhere on the board
GND: C101.2, C102.2, C103.2, C104.2, D101.1 (K), D102.1 (A), D103.1 (A1), R103.2, R106.2, R107.2; also elsewhere on the board
unnamed: D101.2 (A), R105.2
unnamed: R102.2, U11.5 (DEN)
unnamed: R105.1, U11.3 (GND)
unnamed: R101.2, U11.4 (IN)
unnamed: C101.1, R103.1, R104.2, R107.1, U11.6 (IS)
VS: C103.1, C104.1, U11.15 (VS); also elsewhere on the board

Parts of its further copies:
C201, C301, C401: 100pF; C_0402_1005Metric; LCSC C1546
C202, C302, C402: 10nF; C_0402_1005Metric; LCSC C15195
C203, C303, C403: 100nF/100V; C_0805_2012Metric; LCSC C28233
C204, C304, C404: 2.2uF/100V; C_1206_3216Metric; MPN Samsung CL31B225KCHSNNE; LCSC C170101
D201, D301, D401: DSK16; D_SOD-123F; LCSC C22466351
D202, D302, D402: BAT54S; SOT-23; LCSC C7420333
D203, D303, D403: SMAJ30CA; D_SMA; LCSC C19077548; not fitted
R201, R202, R204, R301, R302, R304, R401, R402, R404: 10k; R_0402_1005Metric; LCSC C25744
R203, R207, R303, R307, R403, R407: 1k; R_1206_3216Metric; MPN CRCW12061K00FKEAHP; LCSC C844867
R205, R305, R405: 22; R_0402_1005Metric; LCSC C25092
R206, R306, R406: 47k; R_0603_1608Metric; LCSC C25819; not fitted
U12, U13, U14: BTT6050-1ERA; Infineon_PG-TDSO-14_ThermalVias; LCSC C534868

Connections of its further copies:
+3V3: D202.2 (K), D302.2 (K), D402.2 (K); also elsewhere on the board
/DEN: R202.1, R302.1, R402.1; also elsewhere on the board
/IO3: D202.3 (COM), R204.1; also elsewhere on the board
/IO4: D302.3 (COM), R304.1; also elsewhere on the board
/IO5: D402.3 (COM), R404.1; also elsewhere on the board
/OUT2: C202.1, D203.2 (A2), R206.1, U12.10 (OUT), U12.11 (OUT), U12.12 (OUT); also elsewhere on the board
/OUT3: C302.1, D303.2 (A2), R306.1, U13.10 (OUT), U13.11 (OUT), U13.12 (OUT); also elsewhere on the board
/OUT4: C402.1, D403.2 (A2), R406.1, U14.10 (OUT), U14.11 (OUT), U14.12 (OUT); also elsewhere on the board
/SW_IN2: R201.1; also elsewhere on the board
/SW_IN3: R301.1; also elsewhere on the board
/SW_IN4: R401.1; also elsewhere on the board
GND: C201.2, C202.2, C203.2, C204.2, C301.2, C302.2, C303.2, C304.2, C401.2, C402.2, C403.2, C404.2, D201.1 (K), D202.1 (A), D203.1 (A1), D301.1 (K), D302.1 (A), D303.1 (A1), D401.1 (K), D402.1 (A), D403.1 (A1), R203.2, R206.2, R207.2, R303.2, R306.2, R307.2, R403.2, R406.2, R407.2; also elsewhere on the board
unnamed: D201.2 (A), R205.2
unnamed: D301.2 (A), R305.2
unnamed: D401.2 (A), R405.2
unnamed: R202.2, U12.5 (DEN)
unnamed: R205.1, U12.3 (GND)
unnamed: R201.2, U12.4 (IN)
unnamed: C201.1, R203.1, R204.2, R207.1, U12.6 (IS)
unnamed: R302.2, U13.5 (DEN)
unnamed: R305.1, U13.3 (GND)
unnamed: R301.2, U13.4 (IN)
unnamed: C301.1, R303.1, R304.2, R307.1, U13.6 (IS)
unnamed: R402.2, U14.5 (DEN)
unnamed: R405.1, U14.3 (GND)
unnamed: R401.2, U14.4 (IN)
unnamed: C401.1, R403.1, R404.2, R407.1, U14.6 (IS)
VS: C203.1, C204.1, C303.1, C304.1, C403.1, C404.1, U12.15 (VS), U13.15 (VS), U14.15 (VS); also elsewhere on the board

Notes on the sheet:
BTT6050-1ERA channel (PROFET+24V). Values from datasheet Rev 1.00 application BOM: RIN = RDEN = RSENSE = 10k, CSENSE 100 pF, COUT 10 nF, CVS 100 nF, ZGND = resistor + diode (22R + DSK16). IS: I_IS = I_L / kILIS (~1500); RIS 680R -> ~0.45 V/A at the ADC; fault current 6-40 mA -> clamped to 3V3. Curr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

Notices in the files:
hardware/pdm-4ch/ESP32-PDM-4CH.kicad_pcb:
Hardware licence: CERN-OHL-S v2
rev A 2026-11  CERN-OHL-S v2
